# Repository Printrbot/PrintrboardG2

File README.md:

# Printrboard G2

32bit Controller - Printrbot Simple Pro

#### Klipper

Download the config file and follow the installation instructions.
Requires a Raspberry Pi 3 and Octoprint
[Installation Guide Document](https://docs.google.com/document/d/1a2pSCrTU5F4PQF-cdHiCjmBmUJKTg1H6sDxn2OdDtaw/edit?usp=sharing)

[Klipper Installation Guide](https://www.klipper3d.org/Installation.html)

[Klipper on G2 Github Issue for more information](https://github.com/KevinOConnor/klipper/issues/1121)

##### Steps Per MM vs Step Distance 
   The pound sign is used to comment out code
   Step distance is 1 divided by the microstepping value
   1/80 equals 0.0125 80 steps per mm at 16x microstepping
   Max velocity is around 425 mm/s, however to achieve this speed the bearings must first be run at low speed to warm up.
   [Calibration Calculator](https://vectormfg.net/support/)

#### Stock Firmware
[TinyG](https://github.com/abdrumm/printrbot-docs)

#### Other Firmware - No longer in devlopment 

[Marlin 2.0 - Prints but some setpper driver timing issues still need to be resolved](https://github.com/MarlinFirmware/Marlin/issues/13020)

[ESP3D Gui for the Printrhub Display](https://github.com/luc-github/ESP3D/issues/299)

Powershell Script for Uploading Gcode locally [PrintrBotSelfHost](https://github.com/Printrbot/PrintrBotSelfHost) 

[Printrbot-g2-console](https://github.com/abdrumm/printrbot-docs)

If you wish to remove or bypass the Printrhub
*Power-Enable Pins*

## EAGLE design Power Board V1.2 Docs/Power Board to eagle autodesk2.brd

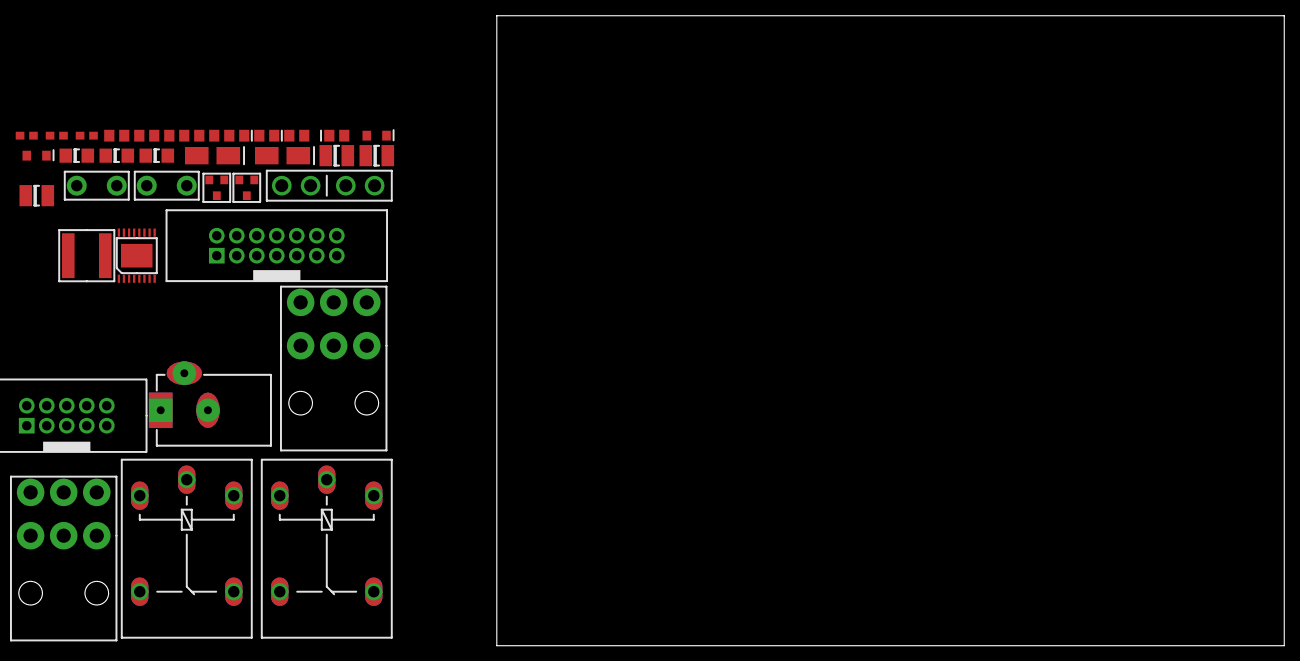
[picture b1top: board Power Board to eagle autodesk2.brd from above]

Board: 2 copper layers, 100.0 x 80.0 mm, 35 parts (0 on the bottom side), 23 nets, no tracks yet.

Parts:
C1, C2, C3: 10uF; CAP_1210
C4: 10nF; CAP_0603
C5: 4.7uF; CAP_0805
C6: 1uF; CAP_0603
C7: 0.47uF; CAP_0603
C8, C9, C10: 22uF; CAP_1206
D1, D2: S1A/B_GEN_PURP_DIODE
D3, D4: Blue; BLUE_LED_0805
D5, D6: DIODE_0805; DIO_0805
F1: BLADE_FUSE_CLIP
J1: PBOARD; 2X5_HEADER_SHROUDED
J2: HUB; 2X7_HEADER_SHROUDED
K1: G5LE
K2: G5LE_4; G5LE
L1: 2.2uH; IND._6X6X2.8MM
R1: 3; RES_0805
R2, R3, R4, R5: 1K; RES_0805
T1, T2: TRANS_PREBIAS_NPN_SOT23-3
U1: LM53603-Q1
U2, U4: MOLEX_6-PIN_PWR
U3: DC_POWER_JACK
U5, U6: 0.250''_MALE_QUICK_CONN; 0.250"_MALE_QUICK_CONN

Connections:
5V: C8.1, C9.1, C10.1, J2.2, L1.2, R1.2, U1.9
12V: C1.1, C2.1, C3.1, C4.1, D1.2, D2.2, K1.1, K1.P, K2.1, K2.P, R2.2, R3.2, U1.11, U1.12, U1.13, U6.1, U6.2
ERASE: J1.6, J2.11
GND: C1.2, C2.2, C3.2, C4.2, C5.2, C6.2, C8.2, C9.2, C10.2, J1.1, J2.1, J2.6, R4.1, R5.1, T1.2, T2.2, U1.6, U1.7, U1.10, U1.15, U1.16, U1.17, U2.4, U2.5, U2.6, U3.2, U3.3, U4.4, U4.5, U4.6
NET_0: F1.1, F1.2, U5.1, U5.2
NET_3: C5.1, U1.4
NET_4: C6.1, R1.1, U1.5
NET_5: C7.1, U1.3
NET_6: C7.2, L1.1, U1.1, U1.2
NET_8: F1.3, F1.4, U2.1, U2.2, U2.3, U3.1
NET_11: D3.1, R2.1
NET_12: D4.1, R3.1
NET_13: D1.1, D3.2, K1.2, T1.3
NET_14: D2.1, D4.2, K2.2, T2.3
NET_21: D6.1, R5.2, T2.1
NET_22: D5.1, R4.2, T1.1
NET_23: D5.2, D6.2, J2.5
RESET: J1.4, J2.13
SWITCHED_12V: K1.S, K2.S, U4.1, U4.2, U4.3
UART_CTS: J1.3, J2.8
UART_RTS: J1.10, J2.10
UART_RX: J1.9, J2.14
UART_TX: J1.7, J2.12

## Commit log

2019-02-13 added gerbers, schematics, marlin and klipper configs
2019-02-13 added more information about firmware
2019-06-05 Klipper config for simple pro
2019-06-05 fix typos
2019-06-05 fixed typos
2019-06-07 simple pro config updates
2019-06-08 updates to config for klipper
2019-06-12 printrbelt config
2019-06-12 Fixes for simple pro
2019-06-13 Added Cura 4.1 Profile for Klipper
2019-07-06 Added M600 Filament change
2019-07-14 Neopixel support
    this adds neo pixel support, currently only works with 1 of 3 leds. The rest will be supported soon.
2019-07-17 new cura profile updates
2019-07-28 fixed heated bed thermistor value typo
2019-07-30 config fixes, cura profiles and more
2019-07-30 fixed typo
2019-07-30 heated bed beheavior notes
    #If you have a heated bed connected to your G2 this code MUST be enabled
    #Otherwise the heated bed will turn on by default this is a bug we will soon fix
    #Remove the section below ONLY if you have disconnected the heated bed power wires
2019-08-23 added config for printers with spring steel bed
    set z min to -7 for spring steel bed sense the probe triggers much earlier then on aluminum.
2019-10-21 Fixed to match hardware correctly
    Fixed the config to match the drive direction mapping for printers in the wild. Previously the motors woud move in the wrong direction when homing.
2019-10-21 Updated version of the Simple Pro Fan Shroud
2019-10-26 Create Printrbot Simple Pro G2 Klipper Config - Leveling HB w Assisted Leveling G266 .txt
    Pressure advance has been tuned for PLA, Assisted leveing using bed screws has been added via G266 this will probe the bed on each corner and prompt the adjustment needed.
2020-01-24 updates for latest version of klipper
2020-02-02 update
    fixed a couple issues for compatibility with latest klipper release
2020-02-02 updated config
    updated to current klipper realease for compatiblity with changes to 20200109 bed_mesh algorithim that uses the probe as the offset refrence instead of the nozzle.
    https://github.com/KevinOConnor/klipper/blob/master/docs/Config_Changes.md
2020-03-25 better probing routine to increase accuracy
    I was having issues with inconsistent probing, I found that the slower the bed is probed the more accurate and repeatable the results will be. Probe z speed is now 1 mm/s, with a 1mm retract between 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
2020-05-05 fixed neopixel macros and other minor changes
2020-06-03 update to support the latest version of klipper
